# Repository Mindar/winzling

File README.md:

# Winzling
Winzling is a tiny electronic load.

## Why?
Why not? I wanted to see just how small I could build an electronic load. Very small as it turns out... About the size of a DIP-12 footprint to be precise. That's smaller than the ATmega328P used on the Arduino UNO. The size could be reduced further by changing a few bits and pieces:

- First off the pin header takes tons of space and creates a routing nightmare (for 2 layer boards). Small 0402-sized solderpads could do the job, they could also placed all over the board, simplifying routing a lot.
- Placing parts (at least some passives) on both PCB sides. This might make routing more difficult though.
- Placing vias under/in solder pads. Vias take up lots of space on both sides of the PCB, sharing that space with solderpads might be a good thing. However I'm not sure how well that works or if it causes any other issues.
- Reflow soldering instead of using a soldering iron. With a soldering iron you always need to consider whether part pins and solderpads are accessible. With reflow soldering that isn't as important anymore. Unfortunately reflow soldering causes other issues (especially with the mosfet's huge heatsink). Maybe a combination of both is the right way.

## How to use it?
Winzling is pretty useless by itself, you need some additional components to use it. Most importantly you need some way to generate the analog signal to set the current, you can do that using an Arduino's PWM output or by using a potentiometer. For a fixed current you could simply use a voltage divider made from two resistors.

### Pinout

Pin names are documented on the back of the board.

Pinname | Description
--------|------------
VCC|5V to power the thing⚡⚡⚡
GND|Ground... 😑
IN+|Positive end of the load⚡
IN-|Negative end of the load (Internally connected to ```GND```)
MEAS|Analog voltage corresponding to the current flowing through the load📊
SET|Analog voltage/PWM input to set the desired load current📏
TEMP|Analog temperature output🌡️

### What to build with it?
You can use Winzling to sink current...

__Warning__: The following is mostly an afterthought. I designed Winzling to be the smallest, cheapest electronic load I could manufacture. Emulating Industrial Sensors was not a design goal.

On a more serious note, you can use it to emulate an industrial sensor using an Arduino. Industrial Sensors often use current loop signalling, which requires the signal to be carried by a current between 4-20 mA. This has several advantages over voltage based signalling<sup>\[1]</sup>:

- Sensors can be powered by the 4 mA minimum current, eliminating the need for additional cables for power <sup>\[2]</sup>
- The signal is not affected by voltage drop over the sensor cable.
- Less vulnerable to noise
- Self monitoring (currents less than 3.8 mA or more than 20.5 mA are taken to indicate a fault. (e.g. cable break -> 0 mA))
- Can be carried over very long cables

<sup>\[1]</sup> [Source (Wikipedia)](https://en.wikipedia.org/wiki/Current_loop)<br>
<sup>\[2]</sup> Winzling does not implement this, but it might still work if you connect ```IN+``` to ```5V``` and connect 5-ish Volt to ```IN+```. If you want to fix this in the PCB design, you could add a small (e.g. SOT-23) 5V linear voltage regulator and connect that to ```IN+``` and ```5V```. I will accept pull requests.

## License
Everything in this git repository is licensed under the following license: <br>
Creative Commons Attribution Share Alike 4.0 International

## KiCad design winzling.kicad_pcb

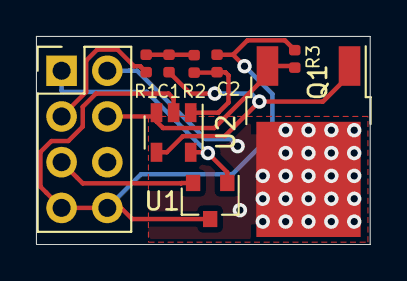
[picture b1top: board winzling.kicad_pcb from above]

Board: 2 copper layers, 18.5 x 11.6 mm, 9 parts (0 on the bottom side), 9 nets.

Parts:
C1, C2: 100nF; C_0402_1005Metric
J1: Connector; PinHeader_2x04_P2.54mm_Vertical
Q1: WSF40N06; TO-252-2
R1, R2: 10k; R_0402_1005Metric
R3: 10R; R_0402_1005Metric
U1: MCP9700T-ETT; SOT-23
U2: LMV611; SOT-23-5

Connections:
+5V: J1.1, U1.1, U2.5
/CONN_V+: J1.2, Q1.2
/cur_sense: J1.4, Q1.3, R3.1, U2.3
/current_set: J1.3, R1.2
/filter_in: C1.1, Q1.1, U2.4
/filter_out: C2.1, R2.1, U2.1
/temp_sense: J1.5, U1.2
GND: C2.2, J1.7, J1.8, R3.2, U1.3, U2.2
unnamed: C1.2, R1.1, R2.2

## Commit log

2019-05-28 added license
2019-05-29 improved documentation and readme
2019-06-23 added pic of finished pcb

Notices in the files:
winzling.kicad_pcb:
alex-s.eu 05/2019 CC-BY-SA
